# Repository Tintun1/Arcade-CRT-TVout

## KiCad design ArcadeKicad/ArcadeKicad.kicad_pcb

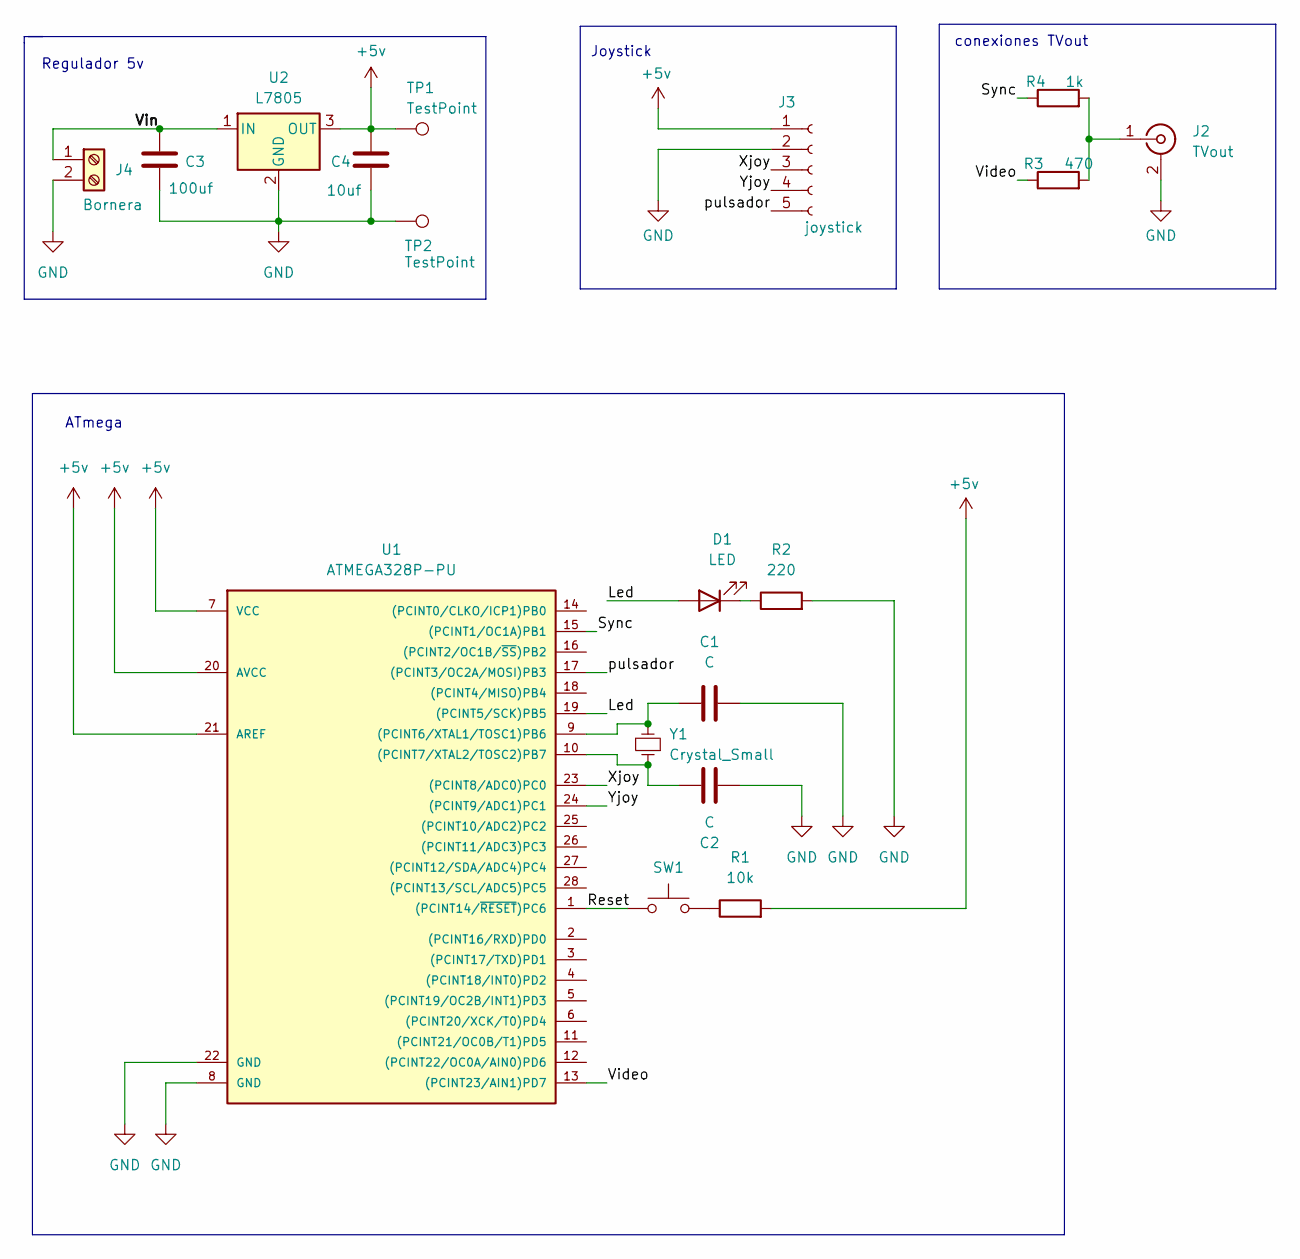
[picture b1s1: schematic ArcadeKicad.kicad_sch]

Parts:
C1, C2: C; C_1210_3225Metric_Pad1.33x2.70mm_HandSolder
C3: 100uf; C_1210_3225Metric_Pad1.33x2.70mm_HandSolder
C4: 10uf; C_1210_3225Metric_Pad1.33x2.70mm_HandSolder
D1: LED; LED_1210_3225Metric
J2: TVout; BNC_Win_364A2x95_Horizontal
J3: joystick; Pin_Strip_5
J4: Bornera; BORNERA2_AZUL
R1: 10k; R_1206
R2: 220; R_1206
R3: 470; R_1206
R4: 1k; R_1206
SW1: SW_Push; SW_SPST_EVQPE1
TP1, TP2: TestPoint; TestPoint_Keystone_5015_Micro-Minature
U1: ATMEGA328P-PU; DIP_28-300_socket
U2: L7805; TSOT-23_HandSoldering
Y1: Crystal_Small; HC49

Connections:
+5v: C4.1, J3.1, R1.2, TP1.1, U1.7 (VCC), U1.20 (AVCC), U1.21 (AREF), U2.3 (OUT)
/Led: D1.2 (A), U1.19 ((PCINT5/SCK)PB5)
/Reset: SW1.1, U1.1 ((PCINT14/~RESET)PC6)
/Sync: R4.1, U1.15 ((PCINT1/OC1A)PB1)
/Video: R3.1, U1.13 ((PCINT23/AIN1)PD7)
/Vin: C3.1, J4.1, U2.1 (IN)
/Xjoy: J3.3, U1.23 ((PCINT8/ADC0)PC0)
/Yjoy: J3.4, U1.24 ((PCINT9/ADC1)PC1)
/pulsador: J3.5, U1.17 ((PCINT3/OC2A/MOSI)PB3)
GND: C1.1, C2.2, C3.2, C4.2, J2.2 (Ext), J3.2, J4.2, R2.2, TP2.1, U1.8 (GND), U1.22 (GND), U2.2 (GND)
unnamed: D1.1 (K), R2.1
unnamed: J2.1 (In), R3.2, R4.2
unnamed: R1.1, SW1.2
unnamed: C1.2, U1.9 ((PCINT6/XTAL1/TOSC1)PB6), Y1.2
unnamed: C2.1, U1.10 ((PCINT7/XTAL2/TOSC2)PB7), Y1.1

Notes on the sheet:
ATmega
Joystick
Regulador 5v
conexiones TVout

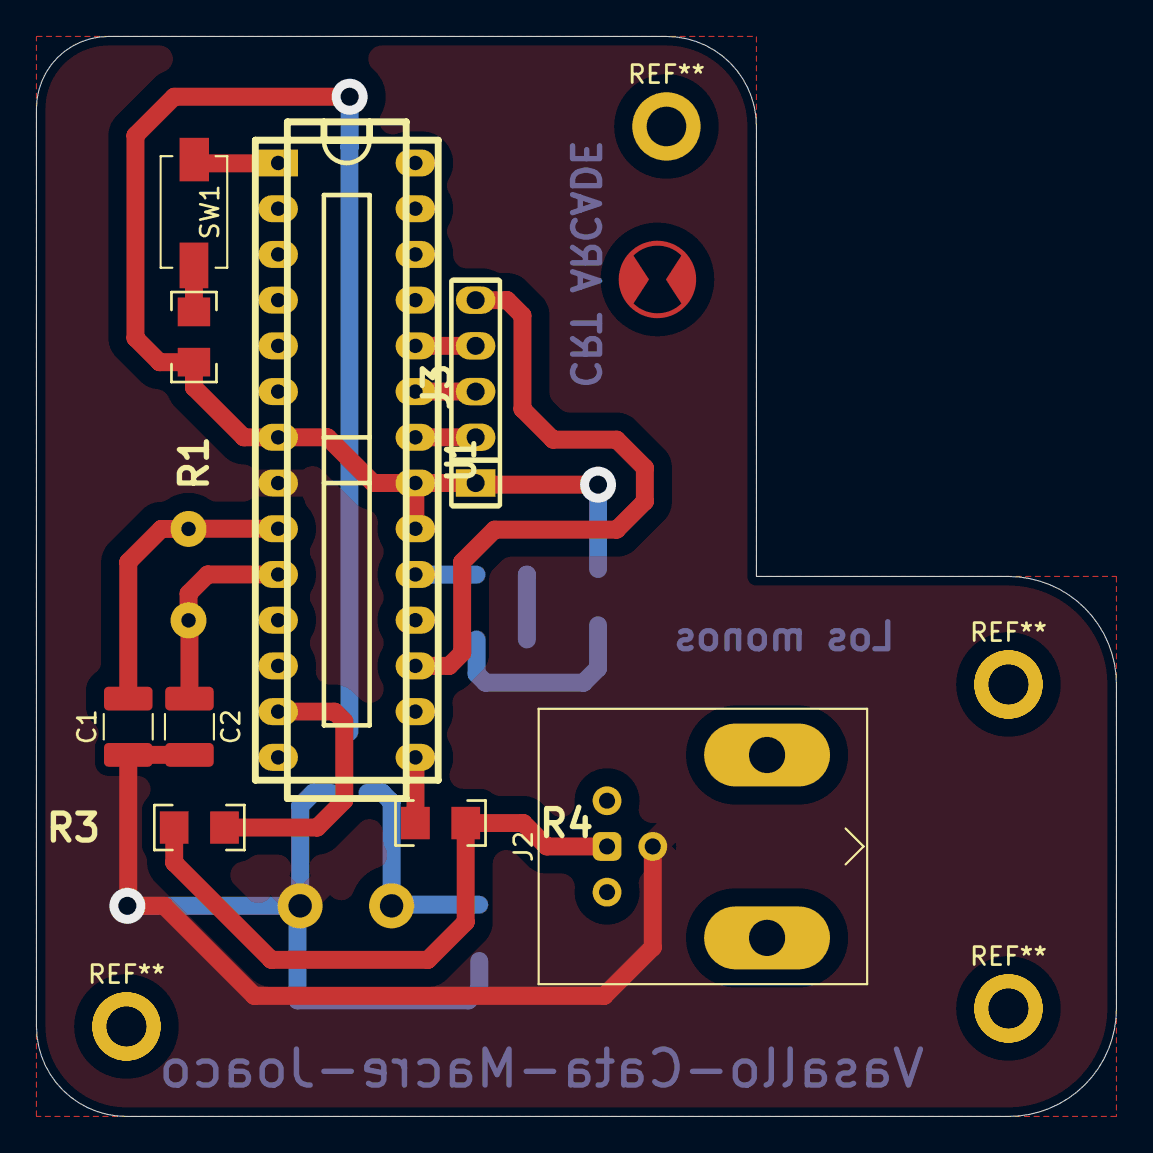
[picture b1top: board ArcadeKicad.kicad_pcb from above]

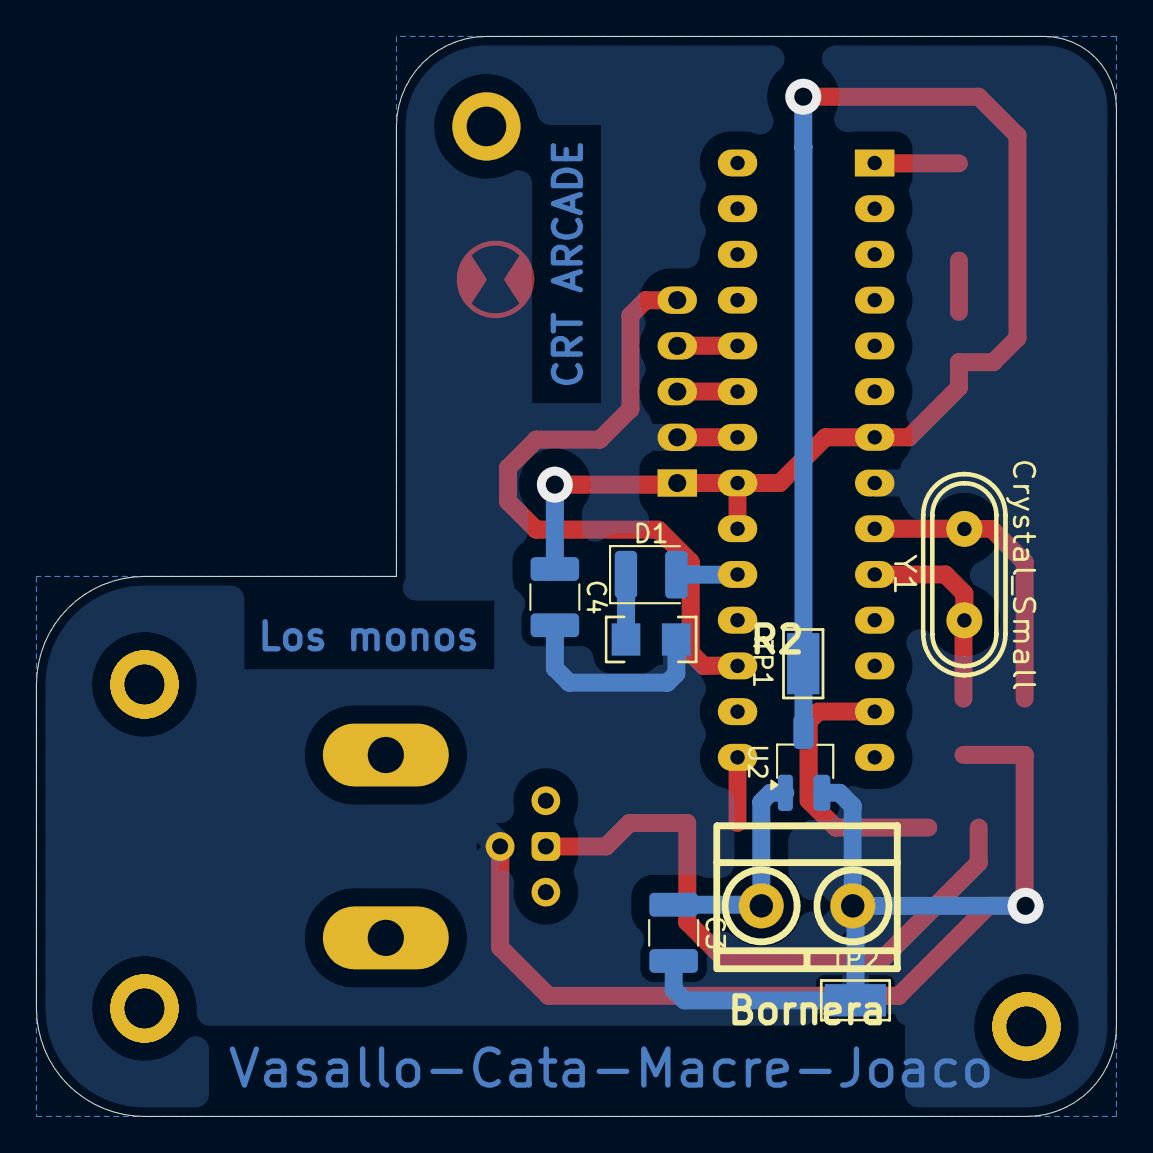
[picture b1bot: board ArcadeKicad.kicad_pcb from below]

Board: 2 copper layers, 60.0 x 60.0 mm, 18 parts (9 on the bottom side), 15 nets.

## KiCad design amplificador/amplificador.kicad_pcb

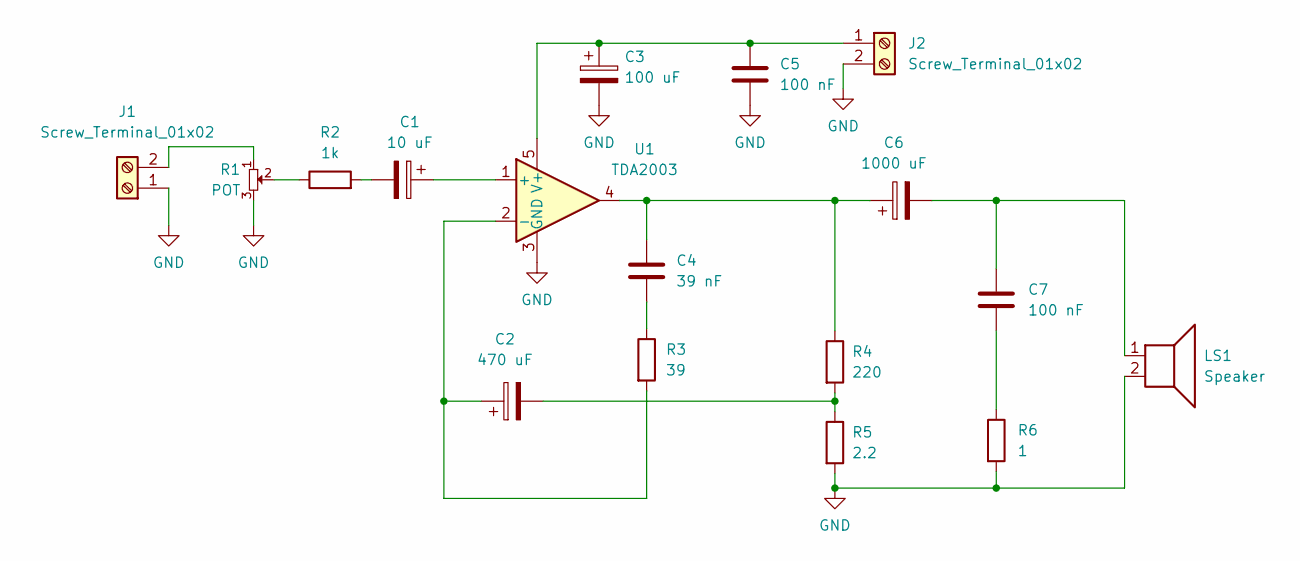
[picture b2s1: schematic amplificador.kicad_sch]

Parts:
C1: 10 uF; CAP_ELEC_8x11.5mm
C2: 470 uF; CAP_ELEC_8x11.5mm
C3: 100 uF; CAP_ELEC_8x11.5mm
C4: 39 nF; C_1206_3216Metric_Pad1.33x1.80mm_HandSolder
C5, C7: 100 nF; C_1206_3216Metric_Pad1.33x1.80mm_HandSolder
C6: 1000 uF; CAP_ELEC_8x11.5mm
J1, J2: Screw_Terminal_01x02; BORNERA2
LS1: Speaker; Speaker_CUI_CMR-1206S-67
R1: POT; Potentiometer_Piher_T-16H_Single_Horizontal
R2: 1k; R_1206
R3: 39; R_1206
R4: 220; R_1206
R5: 2.2; R_1206
R6: 1; R_1206
U1: TDA2003; TO-220-5_P3.4x3.7mm_StaggerOdd_Lead3.8mm_Vertical

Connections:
GND: C3.2, C5.2, J1.1, J2.2, LS1.2, R1.3, R5.2, R6.2, U1.3 (GND)
unnamed: C1.2, R2.2
unnamed: C2.2, R4.2, R5.1
unnamed: C4.1, C6.1, R4.1, U1.4
unnamed: C4.2, R3.1
unnamed: C6.2, C7.1, LS1.1
unnamed: C7.2, R6.1
unnamed: J1.2, R1.1
unnamed: C3.1, C5.1, J2.1, U1.5 (V+)
unnamed: R1.2, R2.1
unnamed: C1.1, U1.1 (+)
unnamed: C2.1, R3.2, U1.2 (-)

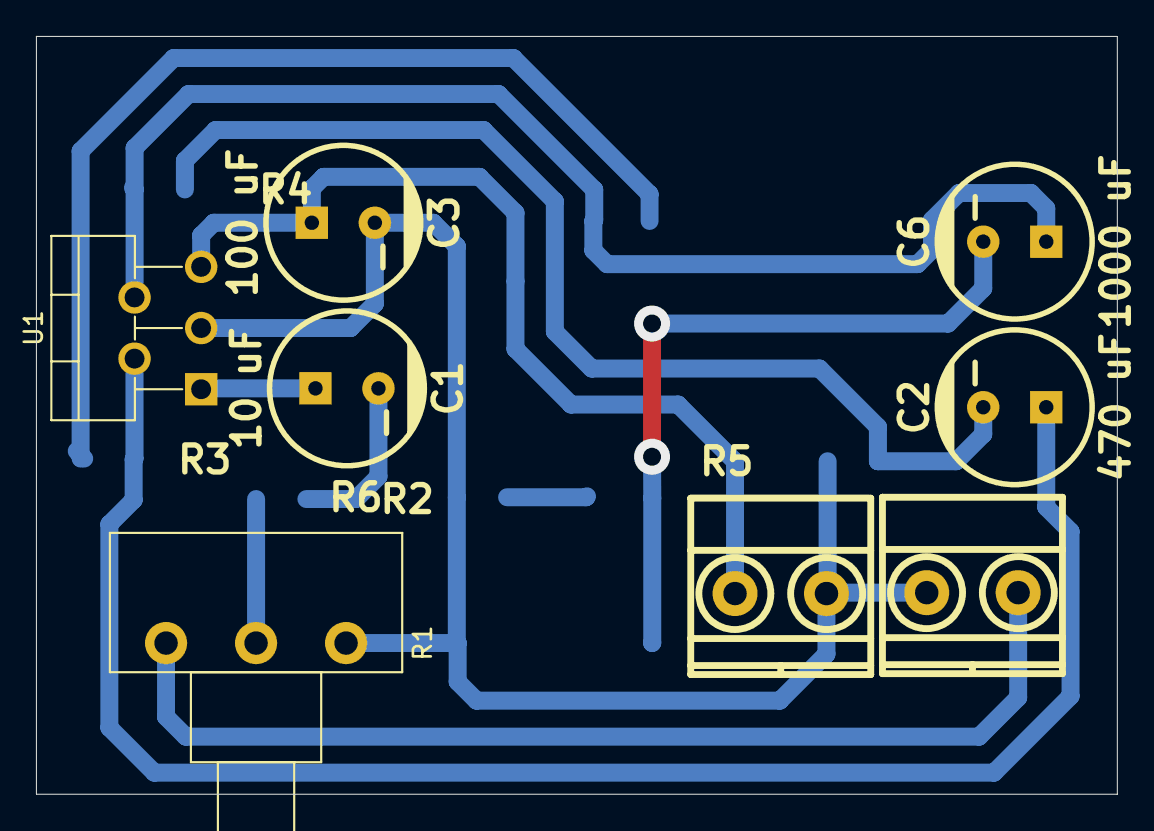
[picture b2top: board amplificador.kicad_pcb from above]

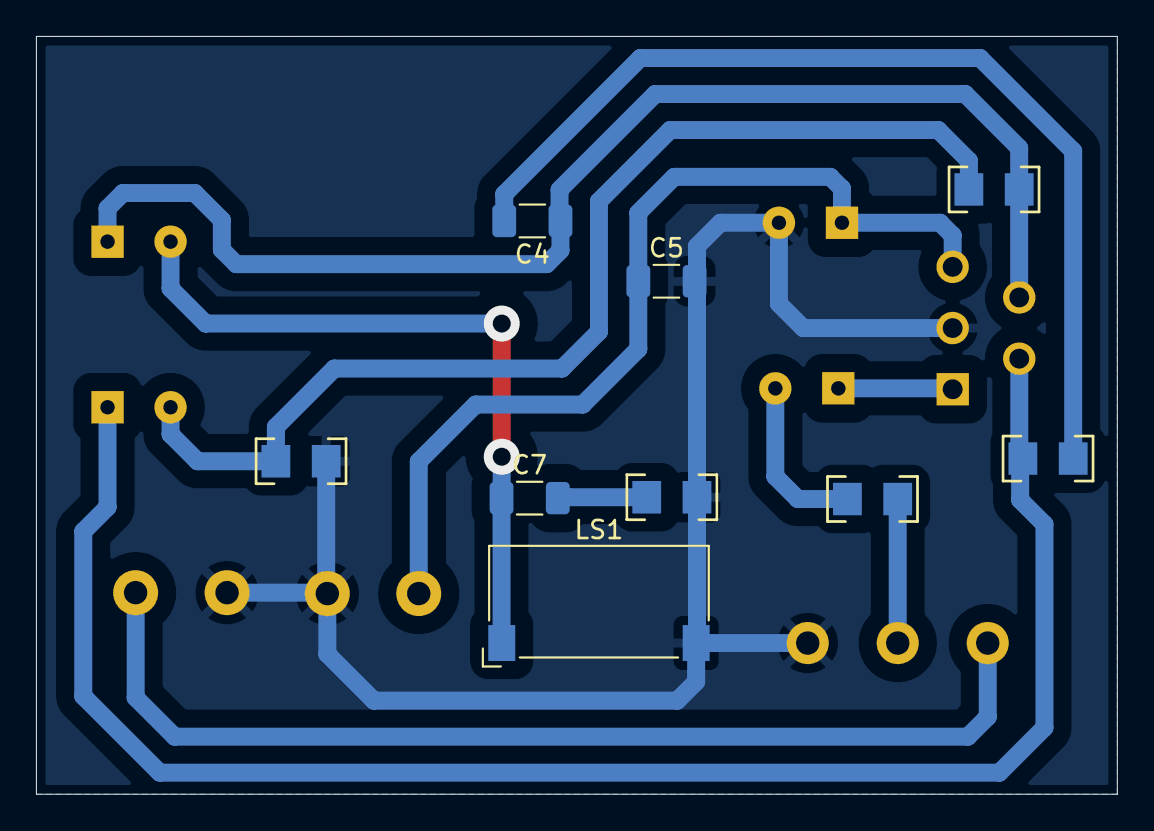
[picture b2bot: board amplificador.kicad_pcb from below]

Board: 2 copper layers, 60.0 x 42.1 mm, 17 parts (9 on the bottom side), 12 nets.

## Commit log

2024-05-30 First commit
    archivos kicad
2024-05-31 PCB
    primer diseño de pcb
2024-06-01 cambios pcb
    agregue los nombres de los integrantes y el simbolo de la paz
2024-06-01 cambio de color pcb 3d
2024-06-06 Programacion
    Subi el codigo del arcade
2024-06-06 Amplificador
    Subi el diseño del amplificador de audio para el arcade
2024-06-16 Plantilla
    plantilla de codigo para un juego destinado con tvout
2024-06-18 Juego reaccion
2024-07-01 Juego reaccion beta 1.0
    Juego reaccion
    - funcionando
    - falta corregir errores de movimiento
    - falta agregar sonido
2024-07-05 actualizacion
    tonos
    vidas
    sprites
    comentarios a sftv
2024-08-29 act
    ultima version con sprites mod
